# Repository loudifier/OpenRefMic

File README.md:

# OpenRefMic

OpenRefMic is an open hardware design for a reference microphone that fits in the popular 1/2" reference microphone form factor, works with consumer microphone interfaces, and meets or exceeds the performance of professional reference microphones at a vastly reduced total system cost.

<br>

## OpenRefMic v2

OpenRefMic version 2 significantly improves the usability of the mic, with integrated frequency response correction, improved PCB layout, and a simpler and more robust mechanical design.

<br>

## Critical specs, typical performance

- Frequency Response: 10Hz-20kHz
    - ±1dB from 10Hz 2.5kHz
    - +4-7dB 10Hz-20kHz raw capsule response
    - ±2dB 10Hz-20kHz with integrated EQ filter
- Noise Floor: 17dBA
- Acoustic Overload Point: 118dBSPL
- Sensitivity: 100mV/Pa
- Dimensions: 12.7x92mm
- Parts cost: $50 (not including 3D printed parts)
- Interface: mini-XLR, 48V phantom power

<br>

### 1/2" microphone comparison

| Mic             | Interface                   | Frequency Response (20-20k)   | Noise Floor | AOP      | Price               |
|-----------------|-----------------------------|-------------------------------|-------------|----------|---------------------|
| OpenRefMic      | 48V phantom power, mini XLR | +3/-7dB (±2dB with EQ)        | 17dBA       | 118dBSPL | Typically <$60      |
| Dayton EMM-6    | 15-48V phantom power, XLR   | ±2dB                          | 36dBA       | 127dBSPL | $60                 |
| MiniDSP U-MIK 2 | USB-C                       | Not specified (likely ±2dB)   | 20dBA       | 125dBSPL | $195 + import       |
| PCB 376A32      | 12-48V phantom power, XLR   | ±2dB                          | 15.5dBA     | 137dBSPL | $1,445              |
| B&K 4191        | 200V Lemo                   | <±1dB                         | 20dBA       | 162dBSPL | Ask for price ($$$) |
| GRAS 46AE       | CCP BNC                     | ±2dB                          | 17dBA       | 138dBSPL | Ask for price ($$$) |

<br>

## Project Overview
The core of the OpenRefMic design is a preamplifier that biases an electret microphone from 48V phantom power, buffers the microphone signal, applies a frequency response correction filter, and to sends the signal to a standard microphone interface. The circuit was designed for the [PUI AOM-5024L-HD-F-R](https://puiaudio.com/file/specs-AOM-5024L-HD-F-R.pdf) low noise microphone capsule, and has been built and tested with that part, but should work with most other electret mics. The schematic and PCB layout were designed in KiCAD and are available in the [Preamplifier section](preamplifier/PREAMPLIFIER.md) of the project, along with the [BOM for all electrical and mechanical parts](Bill_of_materials.csv).

<br>

OpenRefMic construction is simple, consisting of a 3D printed housing, the PCB, mic capsule, screw/nut, and optionally an O-ring and dab of UV cure glue. CAD in Fusion360 and STEP formats are in the [Assembly section](assembly/ASSEMBLY.md), along with STLs for the printed parts and a step-by-step construction guide.

<br>

The noise performance of the complete OpenRefMic prototype far exceeds that of comparably-priced measurement microphones, with a flat frequency response suitable as a reference microphone for measuring speakers, distortion, noise emissions, and capturing field recordings. Raw measurement data, compensation curves, and recommendations for applying calibrations to measurements and recordings are in the [Calibration section](calibration/CALIBRATION.md).

<br>

## Project Goals

### Low noise

This is the most important factor of the OpenRefMic project, and all of the other performance metrics and goals are considered "nice to have". While there are several popular affordable measurement microphones on the market (like the Dayton EMM-6), their noise performance ranges from mediocre to poor. Even professional reference microphones tend to prioritize frequency response flatness over noise performance, and very low noise reference microphones are prohibitively expensive for the hobbyist or self-funded experimenter. The video below is an example of the dramatic difference in noise performance between OpenRefMic and the Dayton EMM-6.

[field recording noise comparison](https://user-images.githubusercontent.com/23405416/175431344-0c36cc5d-fb55-48f4-8029-bcf0d835c0a0.mp4)

Low noise is obviously helpful for applications like field recordings or measuring low-level noise emissions, but one area where microphone noise floor is often overlooked is in speaker distortion measurements. Increasing the stimulus and analysis window or moving the microphone closer to the speaker can help resolve lower distortion levels, but those options may not always be feasible for the given speaker or test setup. The graph below is an example of the differences that you might see between distortion measurements with a typical budget measurement mic with a ~34dBA noise floor and an OpenRefMic with ~18dBA noise floor.

<br>

### Flat, omnidirectional frequency response

A reference microphone should have a frequency response that is flat or characterized well enough that it can be understood how measurements and recordings relate to absolute physical constants. Some aberrations in the off-axis response is expected, particularly at very high frequencies, but the design of the housing, porting, and front grille should minimize directional effects as much as possible. In cases where a flat frequency response is not achievable, the response should be characterized and a process should be defined to apply reciprocal filters to correct recordings.

The microphone element in OpenRefMic has a very low noise floor, but it does not have a flat frequency response. See the calibration page for a compensation curve and filter settings to correct measurements and recordings. 

<br>

### Compatibility with "prosumer" audio interfaces

Professional reference microphones typically require interfaces that are uncommon outside of labratory settings. IEPE current loops over BNC cables on the more affordable end of the spectrum and 200V polarization supplied via LEMO connectors at the other end, where the cable itself is often over $500. The pro audio world has instead standardized on balanced signals and phantom powering over cheap XLR cables, and OpenRefMic is designed to achieve high performance with these affordable interfaces.

<br>

### Low cost

Compatibility with consumer-grade microphone interfaces eliminates the prohibitive costs of an IEPE or LEMO interface, but the parts availability and BOM cost of the microphone itself should be comparable to that of measurement microphones that target the DIY speaker building market. The parts needed to build an OpenRefMic are cheap and, with the low prices of desktop 3D printers and PCB fabrication services, many builders will be able to make their own OpenRefMic for less than they would spend on a budget measurement microphone.

<br>

### 1/2" form factor

Many measurement microphones fit a 1/2" cylindrical form factor, or at least have a long probe end with a 1/2" diameter, which helps maintain omnidirectional frequency response up to several kilohertz. Phantom powering necessitates relatively large capacitors, but the OpenRefMic PCB just barely fits within a 1/2" cross-section. Using a mini-XLR connector, the overall microphone dimensions are 12.7x92mm, almost identical to a reference microphone from B&K or GRAS.

Note that the front grille diameter for OpenRefMic v2 is 13.2mm, which is the de facto standard for professional reference microphones. The slightly increased diameter allows enough space to include an O-ring to seal the mic capsule, threads to actually attach the grille to the mic body, and is wide enough to properly seal to a standard 1/2" pistonphone calibrator.

Specialized shapes for specific applications are left up to individual builders, but please share your design if you would like to add additional form factors to the project.

<br>

### Further goals

- The initial design is based around the PUI AOM-5024L-HD-F-R electret microphone capsule, but designs for additional capsules that trade noise performance for frequency response flatness will be added in the future. The preamplifier as-shown should work with a wide variety of electret mics, and component values can be adjusted for optimal performance or compatibility with analog MEMS mics.
- OpenRefMic prototypes have had normalized frequency respone within ±2dB up to 20kHz, which is typical for commercial measurement microphones. However, absolute sensitivity varies by up to ±3dB, which could introduce significant error in SPL measurements. Professional measurement microphones are calibrated in the field with a pistonphone, a device that you insert the microphone tip into, which generates a tone with a precise frequency and sound pressure level that is consistent for a given sealed air volume. If you have any ideas for a device that could replicate this functionality, or otherwise accurately generate or measure a sound pressure level in order to calibrate an OpenRefMic, please reach out.

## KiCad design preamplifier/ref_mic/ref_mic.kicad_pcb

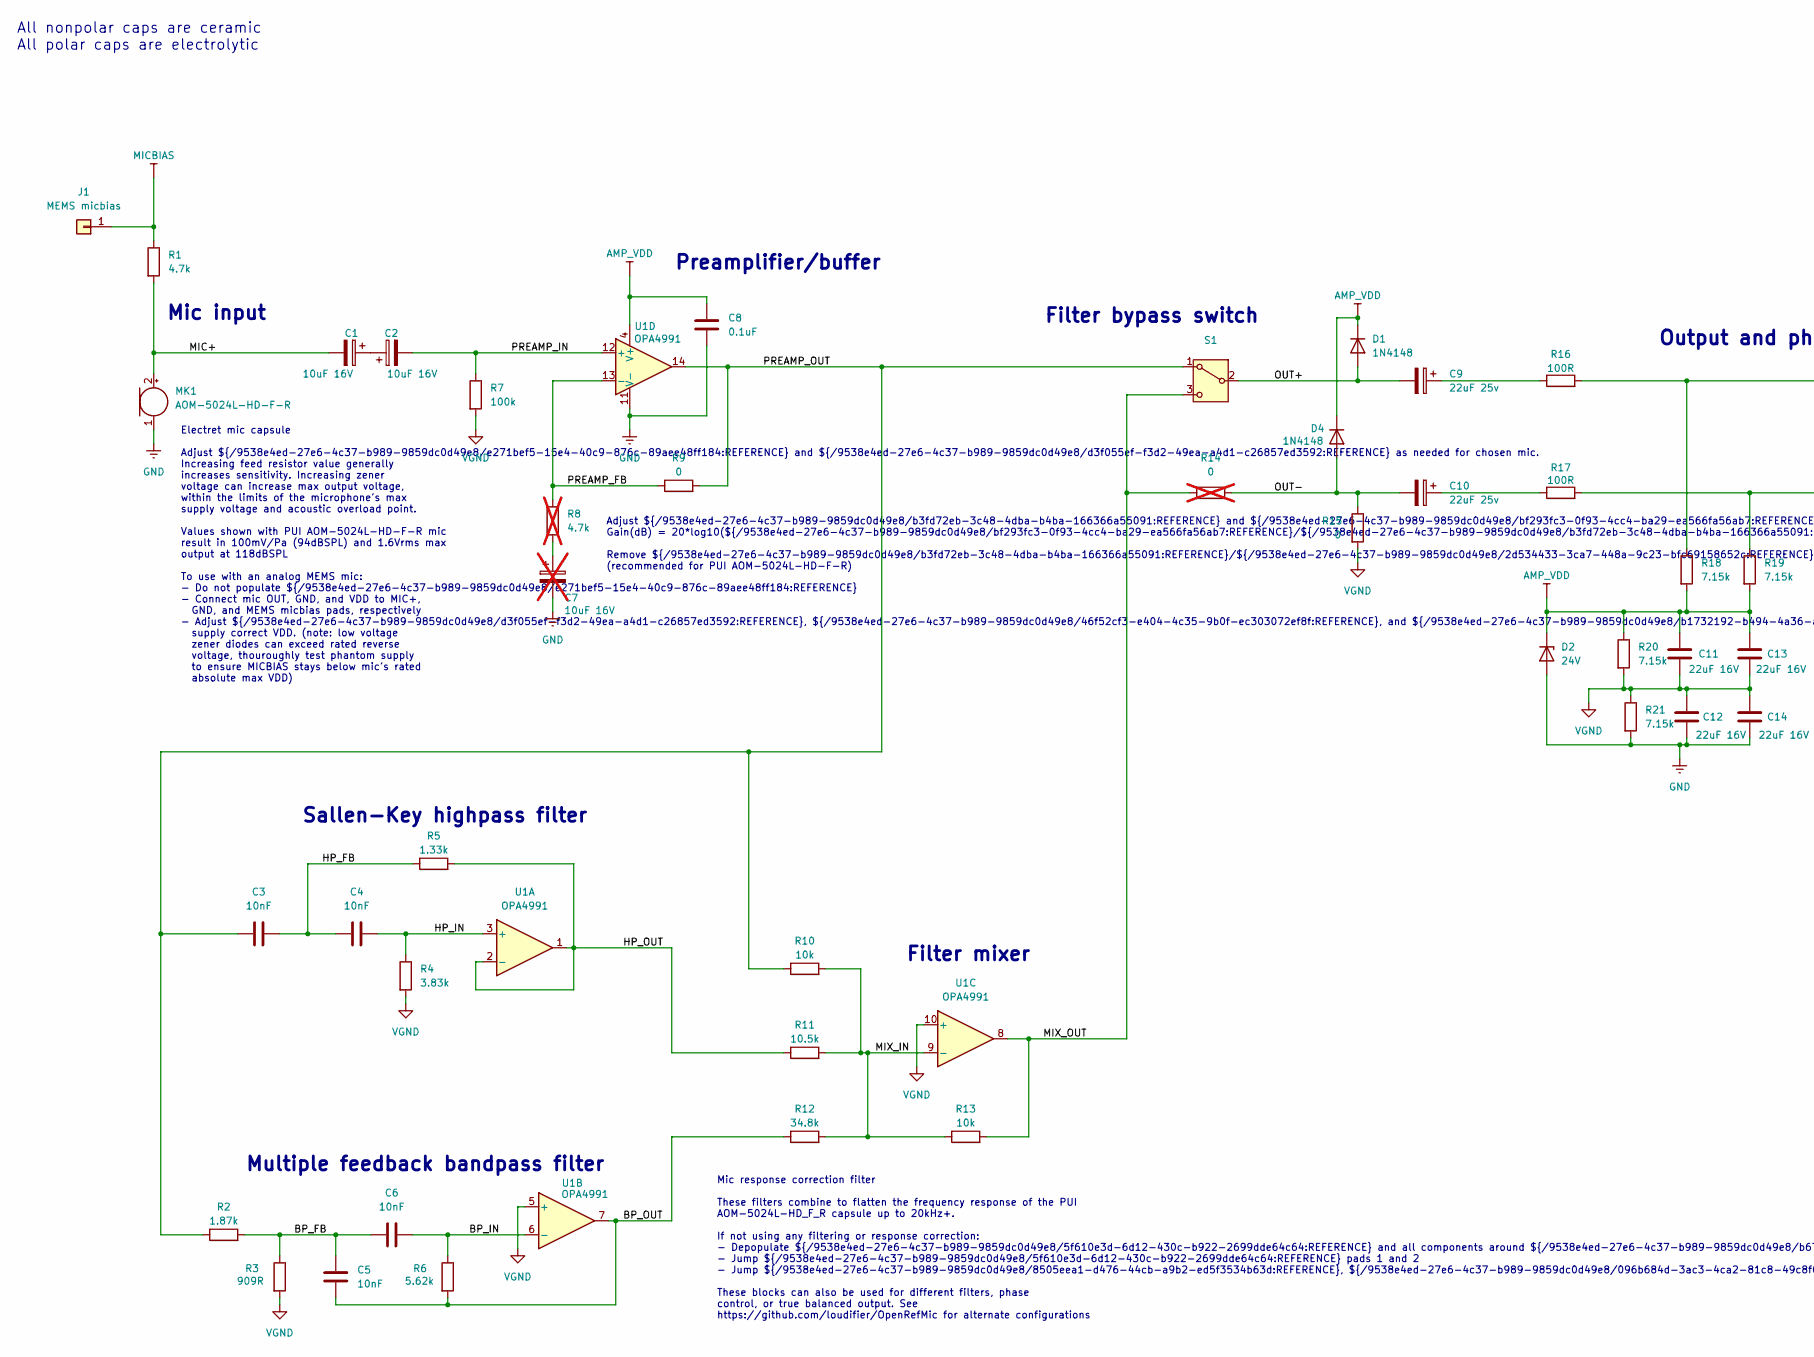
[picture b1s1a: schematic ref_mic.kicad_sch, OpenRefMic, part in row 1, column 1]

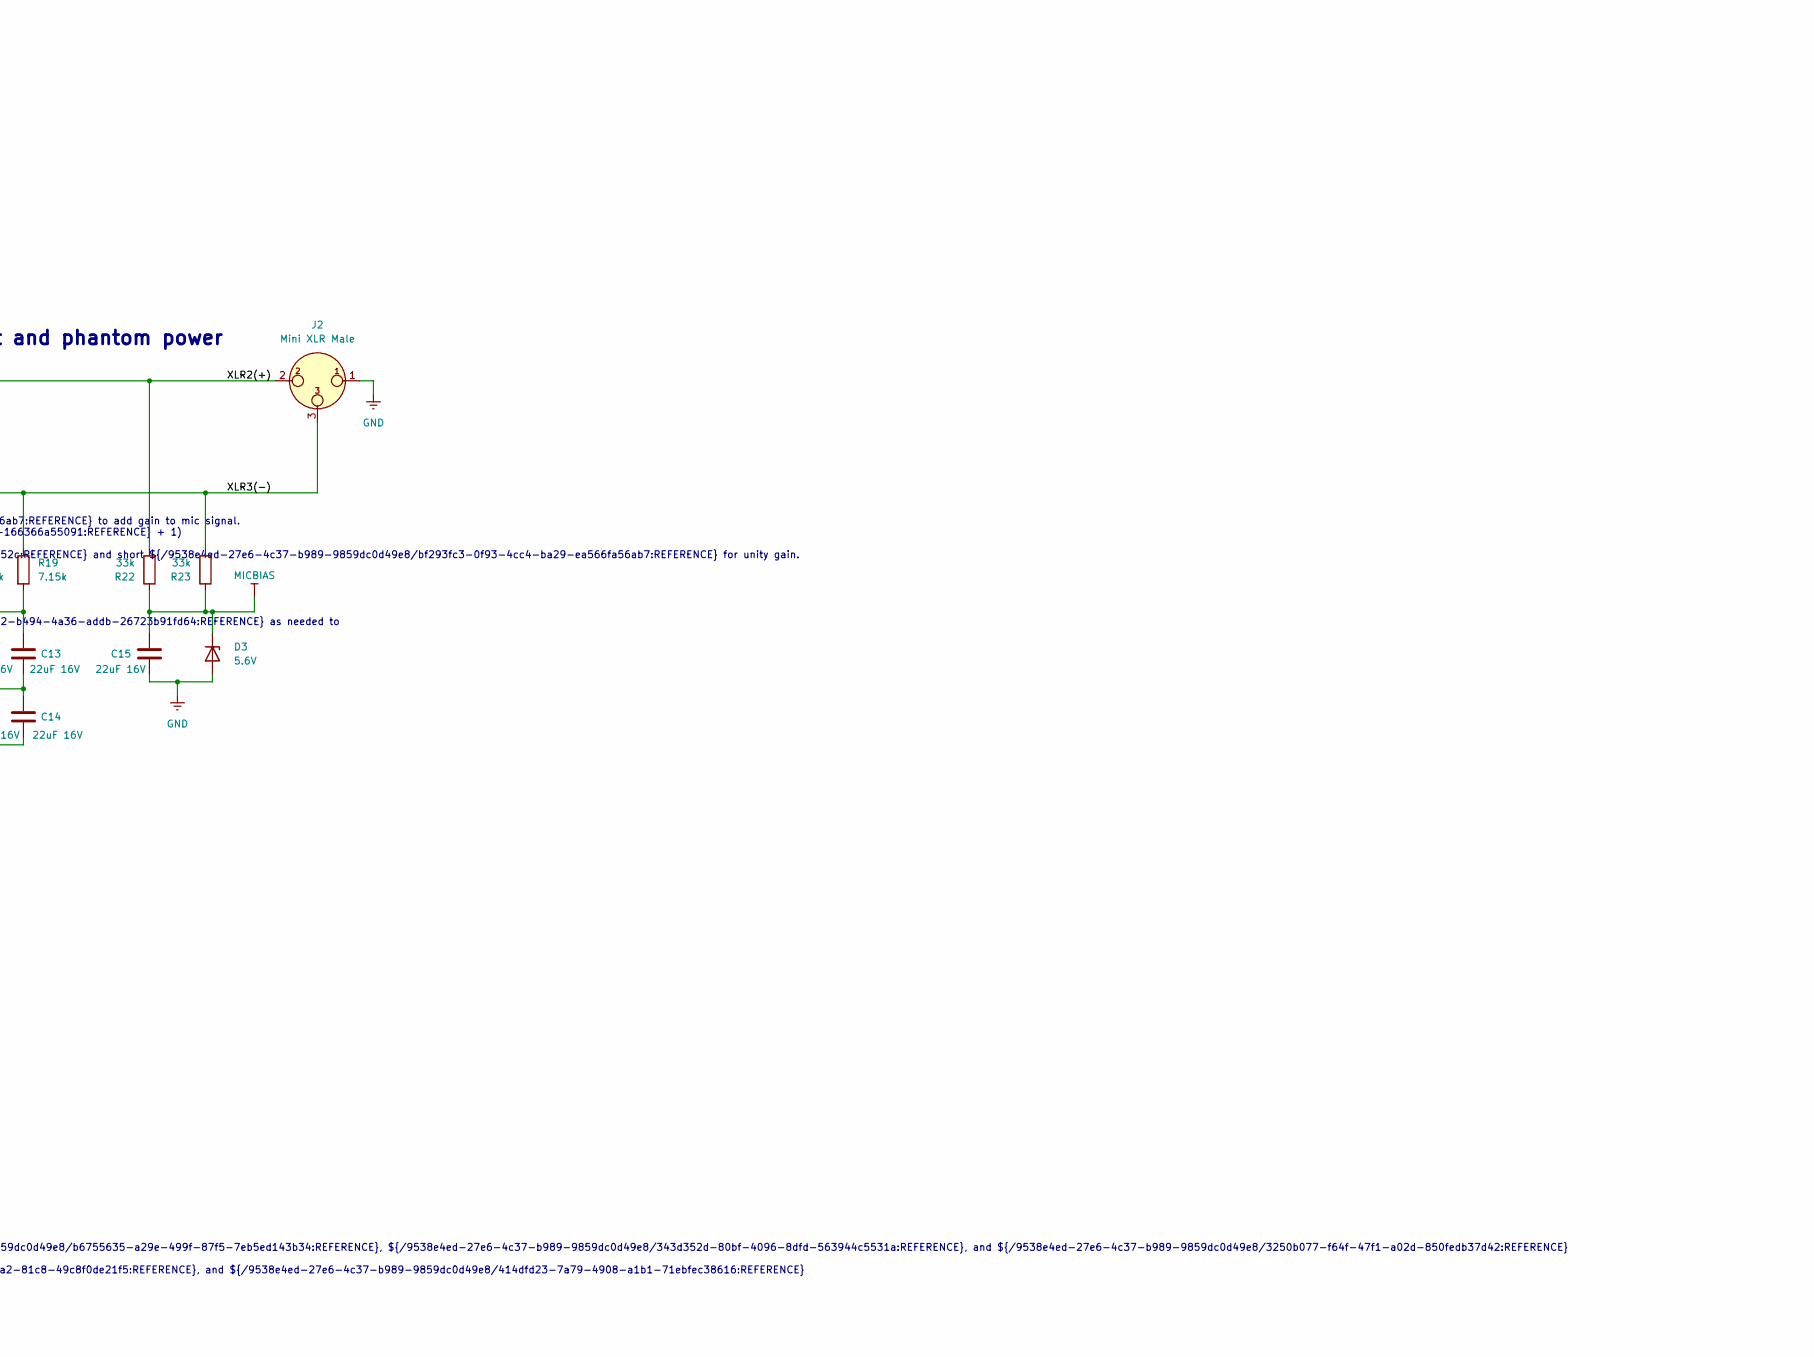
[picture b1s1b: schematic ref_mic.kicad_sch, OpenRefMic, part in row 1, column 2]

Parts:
C1, C2: 10uF 16V; CP_Elec_4x4.5; LCSC_Part_Number Lelon VSS100M1CTR-0404
C3, C4, C5, C6: 10nF; C_0402_1005Metric; LCSC_Part_Number YAGEO CC0402KRX7R9BB103
C7: 10uF 16V; CP_Elec_4x4.5; DigiKey_Part_Number UZG1C100MCL1GB; not fitted
C8: 0.1uF; C_0402_1005Metric; LCSC_Part_Number YAGEO CC0402KRX5R9BB104
C9, C10: 22uF 25v; CP_Elec_6.3x4.5; LCSC_Part_Number Nichicon UZG1E220MCL1GB
C11, C12, C13, C14, C15: 22uF 16V; C_1210_3225Metric_0.95mm-height; DigiKey_Part_Number EMK325BJ226MD-T
D1, D4: 1N4148; D_SOD-523; LCSC_Part_Number MCC 1N4148X-TP
D2: 24V; D_SOD-523; LCSC_Part_Number Diodes Incorporated BZT585B24T-7
D3: 5.6V; D_SOD-523; LCSC_Part_Number Diodes Incorporated BZT52C5V6T-7
J1: MEMS micbias; SolderWire-0.1sqmm_1x01_D0.4mm_OD1mm
J2: Mini XLR Male; Switchcraft_T3BM_edgemount; LCSC_Part_Number Switchcraft TB3M (not normally stocked)
MK1: AOM-5024L-HD-F-R; PinSocket_1x02_P2.54mm_Horizontal; LCSC_Part_Number PUI Audio, Inc. AOM-5024L-HD-F-R (not n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
R1: 4.7k; R_0402_1005Metric; LCSC_Part_Number YAGEO RC0402FR-074K7L
R2: 1.87k; R_0402_1005Metric; LCSC_Part_Number YAGEO RC0402FR-131K87L
R3: 909R; R_0402_1005Metric; LCSC_Part_Number YAGEO RC0402FR-07909RL
R4: 3.83k; R_0402_1005Metric; LCSC_Part_Number YAGEO RC0402FR-073K83L
R5: 1.33k; R_0402_1005Metric; LCSC_Part_Number YAGEO RC0402FR-131K33L
R6: 5.62k; R_0402_1005Metric; LCSC_Part_Number YAGEO RC0402FR-075K62L
R7: 100k; R_0402_1005Metric; LCSC_Part_Number YAGEO RC0402FR-07100KL
R8: 4.7k; R_0402_1005Metric; LCSC_Part_Number YAGEO RC0402FR-074K7L; not fitted
R9, R15: 0; R_0402_1005Metric; LCSC_Part_Number YAGEO RC0402JR-070RL
R10, R13: 10k; R_0402_1005Metric; LCSC_Part_Number YAGEO RC0402FR-0710KL
R11: 10.5k; R_0402_1005Metric; LCSC_Part_Number YAGEO RC0402FR-0710K5L
R12: 34.8k; R_0402_1005Metric; LCSC_Part_Number YAGEO RC0402FR-0734K8L
R14: 0; R_0402_1005Metric; LCSC_Part_Number YAGEO RC0402JR-070RL; not fitted
R16, R17: 100R; R_0402_1005Metric; LCSC_Part_Number YAGEO RC0402FR-07100RL
R18, R19, R20, R21: 7.15k; R_0402_1005Metric; LCSC_Part_Number YAGEO RC0402FR-077K15L
R22, R23: 33k; R_0402_1005Metric; LCSC_Part_Number YAGEO RC0402FR-0733KL
S1: CL-SB-12B-01T; CL-SB-12B-01_NDC; DigiKey_Part_Number CL-SB-12B-01T
U1: OPA4991; SO-14_3.9x8.65mm_P1.27mm; LCSC_Part_Number TI OPA4991IDR

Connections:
/BP_FB: C5.2, C6.1, R2.2, R3.1
/BP_IN: C6.2, R6.1, U1.6 (-)
/BP_OUT: C5.1, R6.2, R12.1, U1.7
/HP_FB: C3.2, C4.1, R5.1
/HP_IN: C4.2, R4.1, U1.3 (+)
/HP_OUT: R5.2, R11.1, U1.1, U1.2 (-)
/MIC+: C1.2, MK1.2 (+), R1.2
/MIX_IN: R10.2, R11.2, R12.2, R13.1, U1.9 (-)
/MIX_OUT: R13.2, R14.1, S1.3 (C), U1.8
/OUT+: C9.2, D1.2 (A), S1.2 (B)
/OUT-: C10.2, D4.2 (A), R14.2, R15.1
/PREAMP_FB: R8.1, R9.1, U1.13 (-)
/PREAMP_IN: C2.2, R7.1, U1.12 (+)
/PREAMP_OUT: C3.1, R2.1, R9.2, R10.1, S1.1 (A), U1.14
/XLR2(+): J2.2, R16.2, R18.1, R22.2
/XLR3(-): J2.3, R17.2, R19.1, R23.2
AMP_VDD: C8.1, C11.1, C13.1, D1.1 (K), D2.1 (K), D4.1 (K), R18.2, R19.2, R20.1, U1.4 (V+)
GND: C7.2, C8.2, C12.2, C14.2, C15.2, D2.2 (A), D3.2 (A), J2.1, MK1.1 (-), R21.2, U1.11 (V-)
MICBIAS: C15.1, D3.1 (K), J1.1, R1.1, R22.1, R23.1
unnamed: C1.1, C2.1
unnamed: C7.1, R8.2
unnamed: C9.1, R16.1
unnamed: C10.1, R17.1
VGND: C11.2, C12.1, C13.2, C14.1, R3.2, R4.2, R7.2, R15.2, R20.2, R21.1, U1.5 (+), U1.10 (+)

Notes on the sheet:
Multiple feedback bandpass filter
All nonpolar caps are ceramic All polar caps are electrolytic
Sallen-Key highpass filter
Mic input
Mic response correction filter These filters combine to flatten the frequency response of the PUI AOM-5024L-HD_F_R capsule up to 20kHz+. If not using any filtering or response correction: - Depopulate ${/9538e4ed-27e6-4c37-b989-9859dc0d49e8/5f610e3d-6d12-430c-b922-2699dde64c64:REFERENCE} and all co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
Preamplifier/buffer
Adjust ${/9538e4ed-27e6-4c37-b989-9859dc0d49e8/b3fd72eb-3c48-4dba-b4ba-166366a55091:REFERENCE} and ${/9538e4ed-27e6-4c37-b989-9859dc0d49e8/bf293fc3-0f93-4cc4-ba29-ea566fa56ab7:REFERENCE} to add gain to mic signal. Gain(dB) = 20*log10(${/9538e4ed-27e6-4c37-b989-9859dc0d49e8/bf293fc3-0f93-4cc4-ba29-e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
Output and phantom power
Electret mic capsule Adjust ${/9538e4ed-27e6-4c37-b989-9859dc0d49e8/e271bef5-15e4-40c9-876c-89aee48ff184:REFERENCE} and ${/9538e4ed-27e6-4c37-b989-9859dc0d49e8/d3f055ef-f3d2-49ea-a4d1-c26857ed3592:REFERENCE} as needed for chosen mic. Increasing feed resistor value generally increases sensitivity. I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
Filter bypass switch
Filter mixer

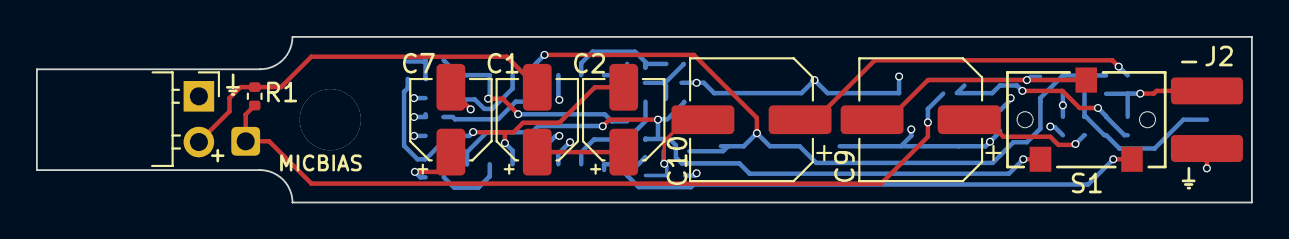
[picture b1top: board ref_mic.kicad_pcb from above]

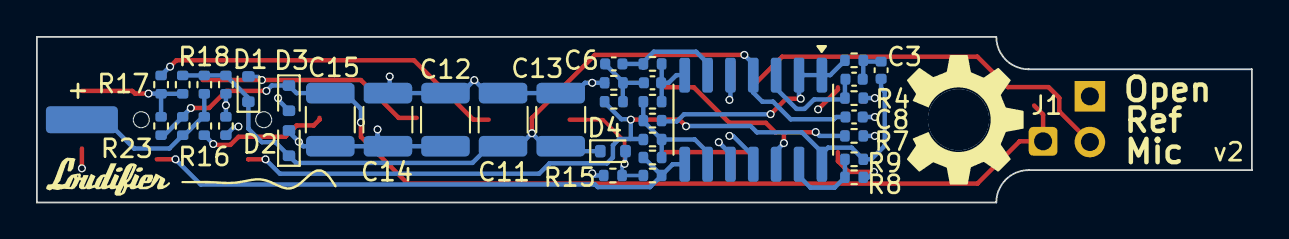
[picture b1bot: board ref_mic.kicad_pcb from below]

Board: 4 copper layers, 67.5 x 9.2 mm, 47 parts (38 on the bottom side), 24 nets.

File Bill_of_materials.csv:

Electrical components,,,,,,
Reference,Value,Qty,DNP,DigiKey_Part_Number,LCSC_Part_Number,Comment
"C1,C2",10uF 16V,2,,UZG1C100MCL1GB,Lelon VSS100M1CTR-0404,
"C3,C4,C5,C6",10nF,4,,CC0402KRX7R9BB103,YAGEO CC0402KRX7R9BB103,
C7,10uF 16V,1,DNP,UZG1C100MCL1GB,Lelon VSS100M1CTR-0404,Populate R8 and C7 to increase gain
C8,0.1uF,1,,CC0402KRX5R9BB104,YAGEO CC0402KRX5R9BB104,
"C9,C10",22uF 25v,2,,UZG1E220MCL1GB,Nichicon UZG1E220MCL1GB,
"C11,C12,C13,C14,C15",22uF 16V,5,,EMK325BJ226MD-T,Taiyo Yuden EMK325BJ226MD-T,
"D1,D4",1N4148,2,,1N4148X-TP,MCC 1N4148X-TP,
D2,24V,1,,BZT585B24T-7,Diodes Incorporated BZT585B24T-7,Zener diode
D3,5.6V,1,,BZT52C5V6T-7,Diodes Incorporated BZT52C5V6T-7,Zener diode
J2,"Mini XLR Male, panel mount",1,,TB3M,Switchcraft TB3M (not normally stocked),Significantly cheaper no-name alternatives available on Amazon/AliExpress
MK1,AOM-5024L-HD-F-R,1,,AOM-5024L-HD-F-R,"PUI Audio, Inc. AOM-5024L-HD-F-R (not normally stocked)",
R1,4.7k,1,,RC0402FR-074K7L,YAGEO RC0402FR-074K7L,
R8,4k7,1,DNP,RC0402FR-074K7L,YAGEO RC0402FR-074K7L,Populate R8 and C7 to increase gain
R2,1.87k,1,,RC0402FR-131K87L,YAGEO RC0402FR-131K87L,
R3,909R,1,,RC0402FR-07909RL,YAGEO RC0402FR-07909RL,
R4,3.83k,1,,RC0402FR-073K83L,YAGEO RC0402FR-073K83L,
R5,1.33k,1,,RC0402FR-131K33L,YAGEO RC0402FR-131K33L,
R6,5.62k,1,,RC0402FR-075K62L,YAGEO RC0402FR-075K62L,
R7,100k,1,,RC0402FR-07100KL,YAGEO RC0402FR-07100KL,
"R9,R15",0,2,,RC0402JR-070RL,YAGEO RC0402JR-070RL,
R14,0,1,DNP,RC0402JR-070RL,YAGEO RC0402JR-070RL,"When not using correction filtering, R14 can be populated for true balanced output (see OpenRefMic project repository for alternate configurations)"
"R10,R13",10k,2,,RC0402FR-0710KL,YAGEO RC0402FR-0710KL,
R11,10.5k,1,,RC0402FR-0710K5L,YAGEO RC0402FR-0710K5L,
"R18,R19,R20,R21",7.15k,4,,RC0402FR-077K15L,YAGEO RC0402FR-077K15L,
R12,34.8k,1,,RC0402FR-0734K8L,YAGEO RC0402FR-0734K8L,
"R16,R17",100R,2,,RC0402FR-07100RL,YAGEO RC0402FR-07100RL,
"R22,R23",33k,2,,RC0402FR-0733KL,YAGEO RC0402FR-0733KL,
S1,CL-SB-12B-01T,1,,CL-SB-12B-01T,Nidec CL-SB-12B-01T,"Switch, single pole double throw"
U1,OPA1664,1,,OPA1664AIDR,TI OPA1664AID,Can substitute with other quad opamp with SOIC-14 package and <~4mA total quiescent current
--,1x2 2.54mm RA female header,1,,PPPC021LGBN-RC,CJT(Changjiang Connectors) A2541HWR-2P,Install in MK1 pads on PCB
--,1x2 2.54mm RA male header,1,,10129379-902002BLF,XFCN PZ254R-11-02P,"Plug into female header, align mic capsule, and solder male pins to mic capsule (see assembly instructions)"
,,,,,,
,,,,,,
Mechanical components,Part,Qty,,McMaster_Part_Number,,Comment
,M3x8 screw,1,,91290A113,,
,M3 nut,1,,98676A100,,
,10.5x1.0mm O-ring,1,,9262K612,,"Fit into groove on interior surface of grille, seals around outside of mic capsule"
,,,,,,
,,,,,,
3D Printed components,Part,Qty,,,,
,Mic body,1,,,,
,Grille,1,,,,
,Top spacer,1,,,,
,Bottom spaker,1,,,,
,,,,,,
,,,,,,
Mini XLR adapter cable,Part,Qty,,DigiKey_Part_Number,LCSC_Part_Number,Comment
,"Mini XLR Female, cable mount",1,,TA3FLX,Switchcraft TA3FLX (not normally stocked),replace full size female connector on standard XLR cable to build a mini XLR adapter cable. Significantly cheaper no-name alternatives available on Amazon/AliExpress

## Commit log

2022-06-19 initial commit
    Majority of initial project and documentation included. Some pieces missing, construction photos, measurement setup and tools descriptions, etc.
2022-06-23 add field recording noise comparison to README.md
2022-06-23 add field recording noise comparison
    fixed markdown so video is properly embedded
2022-08-01 Add R3 to BOM
2022-08-01 Add C3 to BOM
2022-08-13 Update Bill_of_materials.csv
    Moved C3, R3 to optional components section at bottom of BOM. Cleaned up extraneous commas
2023-02-21 a few image updates
2025-03-02 add missing v1 gerbers
2025-03-02 Initial v2 schematic, including high frequency correction filter for specified mic, library for slide switch. Update project to KiCAD 9.0 and change DNPs to use built in DNP feature.
2025-03-02 add note about v2 to readme
2026-01-06 Bulk of v2 updates, before assembly and testing new design - KiCAD project - gerber outputs - schematic PDF - mechanical design (Fusion project, STEP assembly, STL outputs)
2026-01-07 add interactive BOM
2026-02-28 major v2 updates
    fixes based on initial v2 PCB build
    - R6 corrected to 8.06k
    - Replaced opamp with OPA4991
    - Adjust phantom power resistor values to optimize opamp Vdd
    - Connect R15 to VGND to avoid exceeding C10 voltage rating
    - Increase values of input AC-coupling caps, output caps, phantom power caps, decrease output series resistors. Reduces low frequency rolloff
2026-03-19 increase mic body clearance for taller caps
2026-05-18 major v2 updates
    Likely the final versions of v2 design files
    - updated CAD. Small tweaks to spacers, modeled in grille openings (instead of relying on slicer settings), increased room for taller caps, increased clearance for header pins on bottom of PCB
    - Updated EQ component values based on measurements of several prototypes (original v1 prototype capsule response deviated significantly from other 5+ other capsules tested).
    - Added PCB thickness requirement note to preamp doc and directly on fab layer of layout
    - Updated all KiCAD files, gerber outputs, schematic outputs, etc.
    - updated readme, preamp docs
2026-05-24 Update assembly instructions
2026-05-24 update calibration for v2
2026-06-22 add input curve and global gain options to filter optimization

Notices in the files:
preamplifier/ref_mic/ref_mic.kicad_sch:
Loudifier - MIT license - https://github.com/loudifier/OpenRefMic
